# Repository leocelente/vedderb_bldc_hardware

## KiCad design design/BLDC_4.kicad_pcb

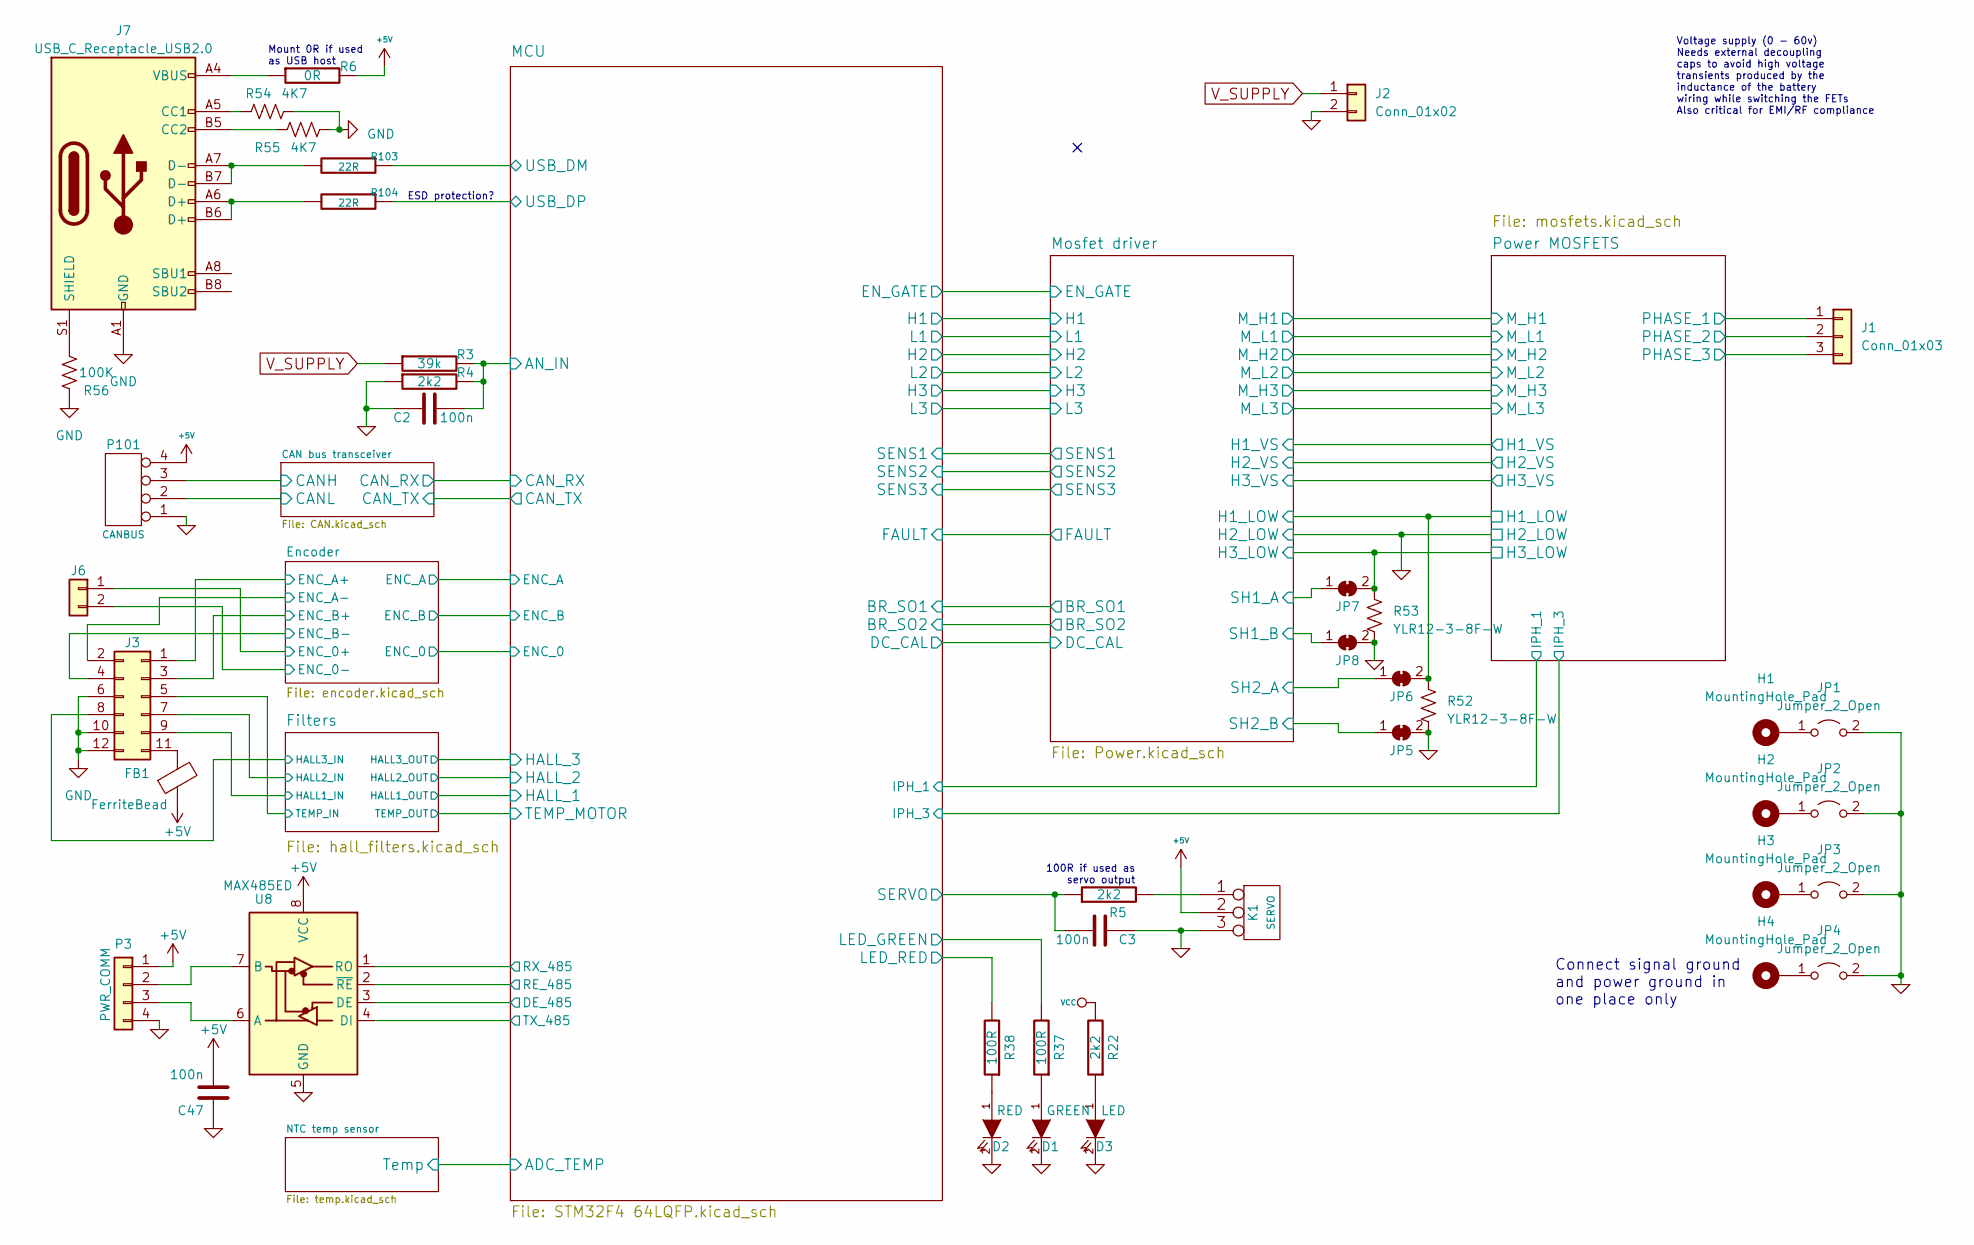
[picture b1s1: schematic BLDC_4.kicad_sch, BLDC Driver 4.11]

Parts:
C2, C3, C47: 100n; SMD-0603_c
D1: GREEN; LED-0603
D2: RED; LED-0603
D3: LED; LED-0603
FB1: FerriteBead; R_0805_2012Metric
H1, H2, H3, H4: MountingHole_Pad; MountingHole_3.2mm_M3_ISO7380_Pad
J1: Conn_01x03; PhoenixContact_MSTBA_2,5_3-G-5,08_1x03_P5.08mm_Horizontal
J2: Conn_01x02; PhoenixContact_MSTBA_2,5_2-G-5,08_1x02_P5.08mm_Horizontal
J3: Conn_02x06_Odd_Even; JST_PHD_S12B-PHDSS_2x06_P2.00mm_Horizontal
J6: Conn_02x06_Odd_Even; JST_PH_S2B-PH-K_1x02_P2.00mm_Horizontal
J7: USB_C_Receptacle_USB2.0; USB_C_Receptacle_G-Switch_GT-USB-7010ASV
JP1, JP2, JP3, JP4: Jumper_2_Open; SolderJumper-2_P1.3mm_Open_Pad1.0x1.5mm
JP5, JP6, JP7, JP8: SolderJumper_2_Bridged; MicroNetSep
K1: SERVO; PinHeader_1x03_P2.54mm_Horizontal
P3: PWR_COMM; JST_PH_S4B-PH-K_1x04_P2.00mm_Horizontal
P101: CANBUS; JST_PH_S4B-PH-K_1x04_P2.00mm_Horizontal
R3: 39k; SMD-0603_r
R4, R5, R22: 2k2; SMD-0603_r
R6: 0R; SMD-0603_r
R37, R38: 100R; SMD-0603_r
R52, R53: YLR12-3-8F-W; YLR2512_G4
R54, R55: 4K7; R_0603_1608Metric_Pad0.98x0.95mm_HandSolder
R56: 100K; R_0603_1608Metric_Pad0.98x0.95mm_HandSolder
R103, R104: 22R; SMD-0603_r
U8: MAX485ED; SOIC-8_3.9x4.9mm_P1.27mm

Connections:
+5V: C47.2, FB1.1, K1.2 (PM), P3.1, P101.4, R6.2, U8.8 (VCC); also elsewhere on the board
/CAN bus transceiver/CANH: P101.3; also elsewhere on the board
/CAN bus transceiver/CANL: P101.2; also elsewhere on the board
/Encoder/ENC_0+: J6.1; also elsewhere on the board
/Encoder/ENC_0-: J6.2; also elsewhere on the board
/Encoder/ENC_A+: J3.1; also elsewhere on the board
/Encoder/ENC_A-: J3.2; also elsewhere on the board
/Encoder/ENC_B+: J3.3; also elsewhere on the board
/Encoder/ENC_B-: J3.4; also elsewhere on the board
/Filters/HALL1_IN: J3.9; also elsewhere on the board
/Filters/HALL2_IN: J3.7; also elsewhere on the board
/Filters/HALL3_IN: J3.8; also elsewhere on the board
/Filters/TEMP_MOTOR: J3.5; also elsewhere on the board
/MCU/AN_IN: C2.2, R3.2, R4.2; also elsewhere on the board
/MCU/DE_485: U8.3 (DE); also elsewhere on the board
/MCU/LED_GREEN: R37.2; also elsewhere on the board
/MCU/LED_RED: R38.2; also elsewhere on the board
/MCU/RE_485: U8.2 (~RE); also elsewhere on the board
/MCU/RX_485: U8.1 (RO); also elsewhere on the board
/MCU/SERVO: C3.2, R5.1; also elsewhere on the board
/MCU/TX_485: U8.4 (DI); also elsewhere on the board
/MCU/USB_DM: R103.1; also elsewhere on the board
/MCU/USB_DP: R104.1; also elsewhere on the board
/Mosfet driver/H1_LOW: JP6.2 (B), R52.1; also elsewhere on the board
/Mosfet driver/H2_VS: J1.2; also elsewhere on the board
/Mosfet driver/SH1_A: JP7.1 (A); also elsewhere on the board
/Mosfet driver/SH2_A: JP6.1 (A); also elsewhere on the board
/Mosfet driver/SH2_B: JP5.1 (A); also elsewhere on the board
/Power MOSFETS/PHASE_1: J1.1; also elsewhere on the board
/Power MOSFETS/PHASE_3: J1.3; also elsewhere on the board
unnamed: D1.1 (A), R37.1
unnamed: D2.1 (A), R38.1
unnamed: D3.1 (A), R22.1
unnamed: FB1.2, J3.11
unnamed: J7.A5 (CC1), R54.1
unnamed: J7.B5 (CC2), R55.1
unnamed: J7.A6 (D+), J7.B6 (D+), R104.2
unnamed: J7.A7 (D-), J7.B7 (D-), R103.2
unnamed: J7.S1 (SHIELD), R56.2
unnamed: J7.A4 (VBUS), J7.A9 (VBUS), J7.B4 (VBUS), J7.B9 (VBUS), R6.1
unnamed: H1.1, JP1.1 (A)
unnamed: H2.1, JP2.1 (A)
unnamed: H3.1, JP3.1 (A)
unnamed: H4.1, JP4.1 (A)
unnamed: K1.1, R5.2
unnamed: P3.2, U8.7 (B)
unnamed: P3.3, U8.6 (A)
VCC: R22.2; also elsewhere on the board
V_SUPPLY: J2.1, R3.1; also elsewhere on the board

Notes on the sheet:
100R if used as servo output
Voltage supply (0 - 60v) Needs external decoupling caps to avoid high voltage transients produced by the inductance of the battery wiring while switching the FETs Also critical for EMI/RF compliance
Connect signal ground and power ground in one place only
Mount 0R if used as USB host
ESD protection?

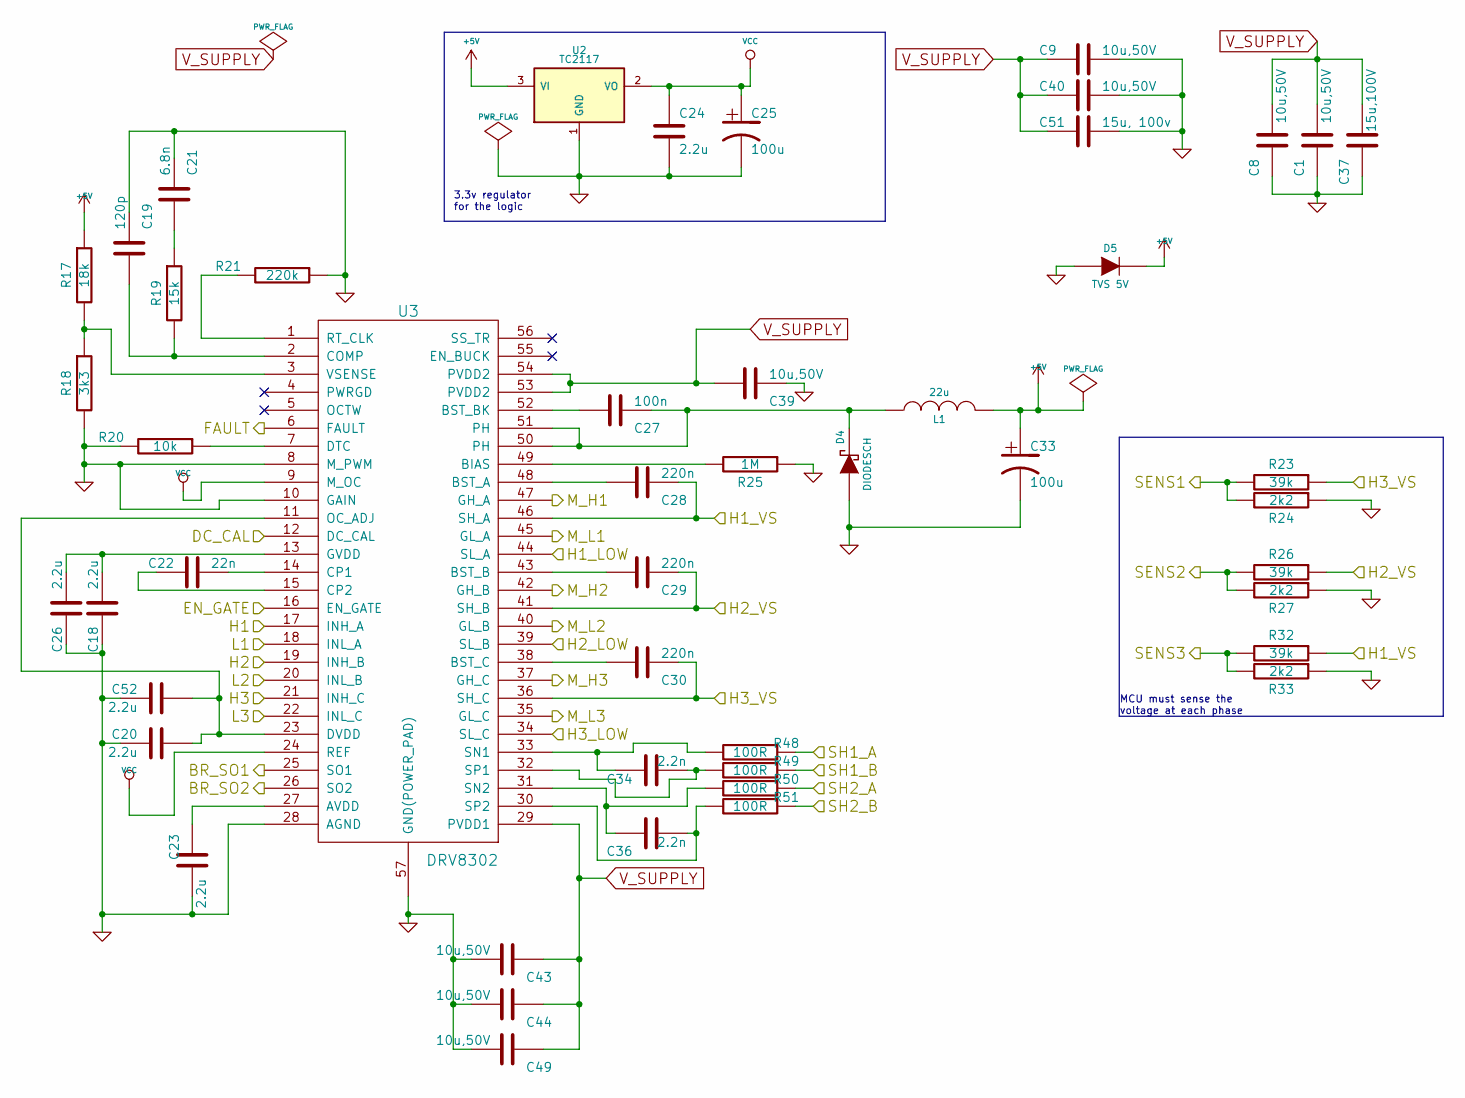
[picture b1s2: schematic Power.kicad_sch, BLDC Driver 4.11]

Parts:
C1, C8, C9, C40, C43, C44, C49: 10u,50V; SMD-1206
C18, C20, C23, C24, C26, C52: 2.2u; SMD-0603_c
C19: 120p; SMD-0603_c
C21: 6.8n; SMD-0603_c
C22: 22n; SMD-0603_c
C25, C33: 100u; c_tant_B
C27: 100n; SMD-0603_c
C28, C29, C30: 220n; SMD-0603_c
C34, C36: 2.2n; SMD-0603_c
C37: 15u,100V; c_2220
C39: 10u,50V; C_1206_3216Metric_Pad1.33x1.80mm_HandSolder
C51: 15u, 100v; c_2220
D4: DIODESCH; SMA_Handsoldering
D5: TVS 5V; do214ac
L1: 22u; inductor_smd_8x5mm
R17: 18k; SMD-0603_r
R18: 3k3; SMD-0603_r
R19: 15k; SMD-0603_r
R20: 10k; SMD-0603_r
R21: 220k; SMD-0603_r
R23, R26, R32: 39k; SMD-0603_r
R24, R27, R33: 2k2; SMD-0603_r
R25: 1M; SMD-0603_r
R48, R49, R50, R51: 100R; SMD-0603_r
U2: TC2117; SOT-223
U3: DRV8302; TSSOP-56-PP

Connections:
+5V: C33.1, D5.2 (K), L1.2, R17.1, U2.3 (VI); also elsewhere on the board
/MCU/BR_SO1: U3.25 (SO1); also elsewhere on the board
/MCU/BR_SO2: U3.26 (SO2); also elsewhere on the board
/MCU/DC_CAL: U3.12 (DC_CAL); also elsewhere on the board
/MCU/EN_GATE: U3.16 (EN_GATE); also elsewhere on the board
/MCU/FAULT: U3.6 (FAULT); also elsewhere on the board
/MCU/H1: U3.17 (INH_A); also elsewhere on the board
/MCU/H2: U3.19 (INH_B); also elsewhere on the board
/MCU/H3: U3.21 (INH_C); also elsewhere on the board
/MCU/L1: U3.18 (INL_A); also elsewhere on the board
/MCU/L2: U3.20 (INL_B); also elsewhere on the board
/MCU/L3: U3.22 (INL_C); also elsewhere on the board
/MCU/SENS1: R23.2, R24.2; also elsewhere on the board
/MCU/SENS2: R26.2, R27.2; also elsewhere on the board
/MCU/SENS3: R32.2, R33.2; also elsewhere on the board
/Mosfet driver/H1_LOW: U3.44 (SL_A); also elsewhere on the board
/Mosfet driver/H2_VS: C29.1, R26.1, U3.41 (SH_B); also elsewhere on the board
/Mosfet driver/M_H1: U3.47 (GH_A); also elsewhere on the board
/Mosfet driver/M_H2: U3.42 (GH_B); also elsewhere on the board
/Mosfet driver/M_H3: U3.37 (GH_C); also elsewhere on the board
/Mosfet driver/M_L1: U3.45 (GL_A); also elsewhere on the board
/Mosfet driver/M_L2: U3.40 (GL_B); also elsewhere on the board
/Mosfet driver/M_L3: U3.35 (GL_C); also elsewhere on the board
/Mosfet driver/SH1_A: R48.1; also elsewhere on the board
/Mosfet driver/SH2_A: R50.1; also elsewhere on the board
/Mosfet driver/SH2_B: R51.1; also elsewhere on the board
unnamed: C21.2, R19.1
unnamed: C27.1, D4.2 (K), L1.1, U3.50 (PH), U3.51 (PH)
unnamed: C23.2, U3.27 (AVDD)
unnamed: R25.2, U3.49 (BIAS)
unnamed: C28.2, U3.48 (BST_A)
unnamed: C29.2, U3.43 (BST_B)
unnamed: C27.2, U3.52 (BST_BK)
unnamed: C30.2, U3.38 (BST_C)
unnamed: C19.2, R19.2, U3.2 (COMP)
unnamed: C22.1, U3.14 (CP1)
unnamed: C22.2, U3.15 (CP2)
unnamed: R20.1, U3.7 (DTC)
unnamed: C20.2, C52.2, U3.11 (OC_ADJ), U3.23 (DVDD)
unnamed: C18.1, C26.1, U3.13 (GVDD)
unnamed: R21.2, U3.1 (RT_CLK)
unnamed: C34.1, R48.2, U3.33 (SN1)
unnamed: C36.1, R50.2, U3.31 (SN2)
unnamed: C34.2, R49.2, U3.32 (SP1)
unnamed: C36.2, R51.2, U3.30 (SP2)
unnamed: R17.2, R18.1, U3.3 (VSENSE)
VCC: C24.1, C25.1, U2.2 (VO), U3.9 (M_OC), U3.24 (REF); also elsewhere on the board
V_SUPPLY: C1.2, C8.2, C9.2, C37.2, C39.2, C40.2, C43.1, C44.1, C49.1, C51.2, U3.29 (PVDD1), U3.53 (PVDD2), U3.54 (PVDD2); also elsewhere on the board

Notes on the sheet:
3.3v regulator for the logic
MCU must sense the voltage at each phase

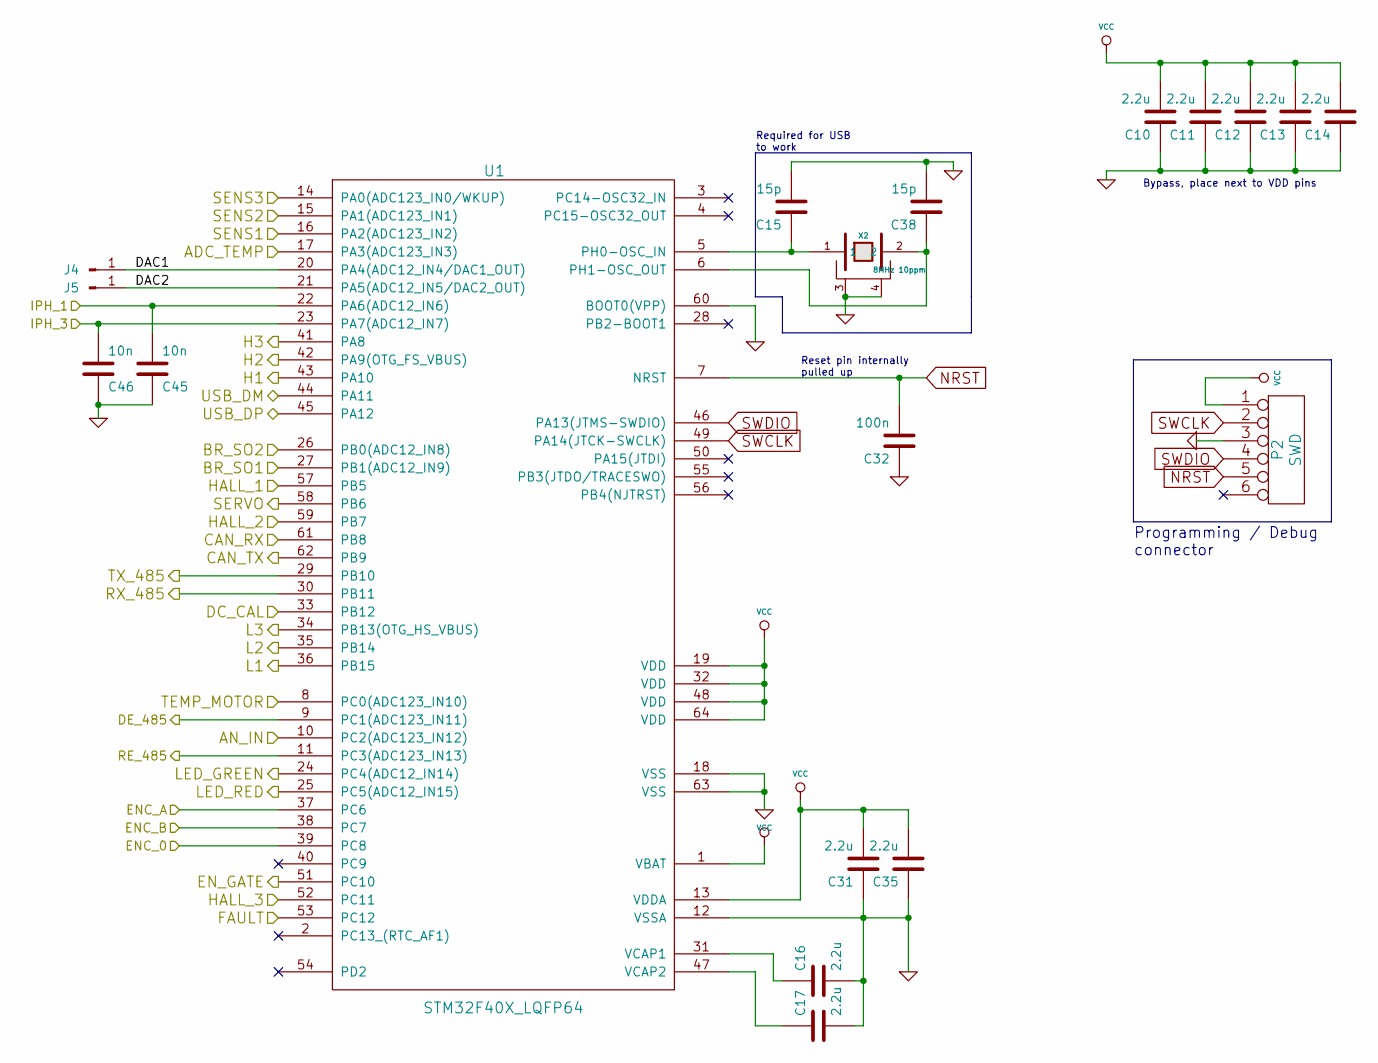
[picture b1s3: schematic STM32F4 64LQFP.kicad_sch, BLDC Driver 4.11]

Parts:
C10, C11, C12, C13, C14, C16, C17, C31, C35: 2.2u; SMD-0603_c
C15, C38: 15p; SMD-0603_c
C32: 100n; SMD-0603_c
C45, C46: 10n; SMD-0603_c
J4, J5: Conn_01x01_Pin; PinHeader_1x01_P1.00mm_Vertical
P2: SWD; JST_PH_B6B-PH-K_1x06_P2.00mm_Vertical
U1: STM32F40X_LQFP64; lqfp64_pad_mod
X2: 8MHz 10ppm; Crystal_5x3mm; mfg# ABM3B-8.0-10-1UT

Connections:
/CAN bus transceiver/CAN_RX: U1.61 (PB8); also elsewhere on the board
/CAN bus transceiver/CAN_TX: U1.62 (PB9); also elsewhere on the board
/Encoder/ENC_0: U1.39 (PC8); also elsewhere on the board
/Encoder/ENC_A: U1.37 (PC6); also elsewhere on the board
/Encoder/ENC_B: U1.38 (PC7); also elsewhere on the board
/Filters/HALL1_OUT: U1.57 (PB5); also elsewhere on the board
/Filters/HALL2_OUT: U1.59 (PB7); also elsewhere on the board
/Filters/HALL3_OUT: U1.52 (PC11); also elsewhere on the board
/Filters/TEMP_MOTOR: U1.8 (PC0(ADC123_IN10)); also elsewhere on the board
/MCU/ADC_TEMP: U1.17 (PA3(ADC123_IN3)); also elsewhere on the board
/MCU/AN_IN: U1.10 (PC2(ADC123_IN12)); also elsewhere on the board
/MCU/BR_SO1: U1.27 (PB1(ADC12_IN9)); also elsewhere on the board
/MCU/BR_SO2: U1.26 (PB0(ADC12_IN8)); also elsewhere on the board
/MCU/DAC1: J4.1, U1.20 (PA4(ADC12_IN4/DAC1_OUT))
/MCU/DAC2: J5.1, U1.21 (PA5(ADC12_IN5/DAC2_OUT))
/MCU/DC_CAL: U1.33 (PB12); also elsewhere on the board
/MCU/DE_485: U1.9 (PC1(ADC123_IN11)); also elsewhere on the board
/MCU/EN_GATE: U1.51 (PC10); also elsewhere on the board
/MCU/FAULT: U1.53 (PC12); also elsewhere on the board
/MCU/H1: U1.43 (PA10); also elsewhere on the board
/MCU/H2: U1.42 (PA9(OTG_FS_VBUS)); also elsewhere on the board
/MCU/H3: U1.41 (PA8); also elsewhere on the board
/MCU/IPH_1: C45.2, U1.22 (PA6(ADC12_IN6)); also elsewhere on the board
/MCU/IPH_3: C46.2, U1.23 (PA7(ADC12_IN7)); also elsewhere on the board
/MCU/L1: U1.36 (PB15); also elsewhere on the board
/MCU/L2: U1.35 (PB14); also elsewhere on the board
/MCU/L3: U1.34 (PB13(OTG_HS_VBUS)); also elsewhere on the board
/MCU/LED_GREEN: U1.24 (PC4(ADC12_IN14)); also elsewhere on the board
/MCU/LED_RED: U1.25 (PC5(ADC12_IN15)); also elsewhere on the board
/MCU/RE_485: U1.11 (PC3(ADC123_IN13)); also elsewhere on the board
/MCU/RX_485: U1.30 (PB11); also elsewhere on the board
/MCU/SENS1: U1.16 (PA2(ADC123_IN2)); also elsewhere on the board
/MCU/SENS2: U1.15 (PA1(ADC123_IN1)); also elsewhere on the board
/MCU/SENS3: U1.14 (PA0(ADC123_IN0/WKUP)); also elsewhere on the board
/MCU/SERVO: U1.58 (PB6); also elsewhere on the board
/MCU/TX_485: U1.29 (PB10); also elsewhere on the board
/MCU/USB_DM: U1.44 (PA11); also elsewhere on the board
/MCU/USB_DP: U1.45 (PA12); also elsewhere on the board
NRST: C32.2, P2.5, U1.7 (NRST)
unnamed: C15.1, U1.5 (PH0-OSC_IN), X2.1
unnamed: C38.1, U1.6 (PH1-OSC_OUT), X2.2
unnamed: C16.1, U1.31 (VCAP1)
unnamed: C17.1, U1.47 (VCAP2)
SWCLK: P2.2, U1.49 (PA14(JTCK-SWCLK))
SWDIO: P2.4, U1.46 (PA13(JTMS-SWDIO))
VCC: C10.2, C11.2, C12.2, C13.2, C14.2, C31.2, C35.2, P2.1, U1.1 (VBAT), U1.13 (VDDA), U1.19 (VDD), U1.32 (VDD), U1.48 (VDD), U1.64 (VDD); also elsewhere on the board

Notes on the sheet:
Bypass, place next to VDD pins
Required for USB to work
Programming / Debug connector
Reset pin internally pulled up

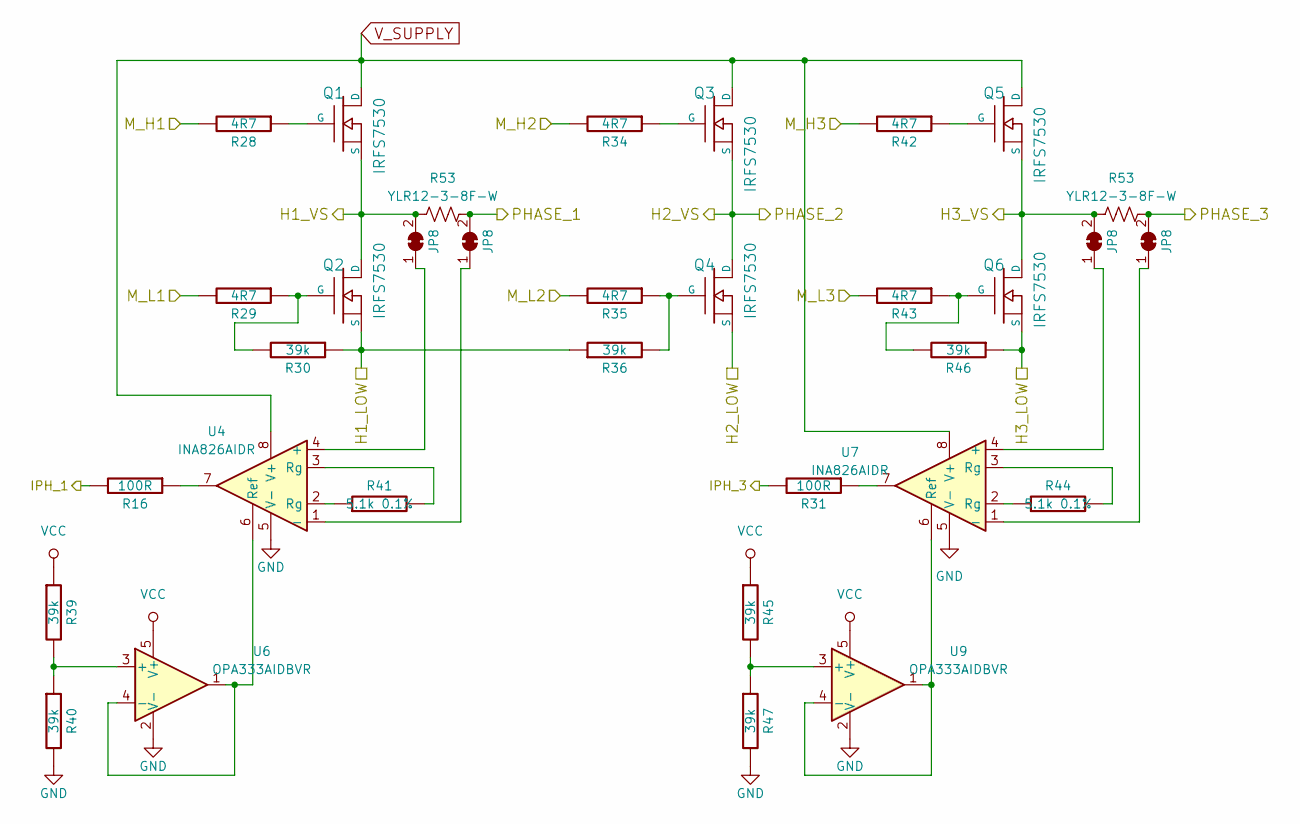
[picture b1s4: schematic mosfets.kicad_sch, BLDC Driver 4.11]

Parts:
JP8: SolderJumper_2_Bridged; MicroNetSep
Q1, Q2, Q3, Q4, Q5, Q6: IRFS7530; D2PAK-7-GDS
R16, R31: 100R; SMD-0603_r
R28, R29, R34, R35, R42, R43: 4R7; SMD-0603_r
R30, R36, R39, R40, R45, R46, R47: 39k; SMD-0603_r
R41, R44: 5.1k 0.1%; SMD-0603_r
R53: YLR12-3-8F-W; YLR2512_G4
U4, U7: INA826AIDR; SOIC-8_3.9x4.9mm_P1.27mm
U6, U9: OPA333AIDBVR; SOT-23-5

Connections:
/MCU/IPH_1: R16.2; also elsewhere on the board
/MCU/IPH_3: R31.2; also elsewhere on the board
/Mosfet driver/H1_LOW: Q2.S, R30.1, R36.1; also elsewhere on the board
/Mosfet driver/H2_VS: Q3.S, Q4.D; also elsewhere on the board
/Mosfet driver/M_H1: R28.2; also elsewhere on the board
/Mosfet driver/M_H2: R34.2; also elsewhere on the board
/Mosfet driver/M_H3: R42.2; also elsewhere on the board
/Mosfet driver/M_L1: R29.2; also elsewhere on the board
/Mosfet driver/M_L2: R35.2; also elsewhere on the board
/Mosfet driver/M_L3: R43.2; also elsewhere on the board
unnamed: Q1.G, R28.1
unnamed: Q2.G, R29.1, R30.2
unnamed: Q3.G, R34.1
unnamed: Q4.G, R35.1, R36.2
unnamed: Q5.G, R42.1
unnamed: Q6.G, R43.1, R46.2
unnamed: R16.1, U4.7
unnamed: R31.1, U7.7
unnamed: R41.1, U4.2 (Rg)
unnamed: R41.2, U4.3 (Rg)
unnamed: R44.1, U7.2 (Rg)
unnamed: R44.2, U7.3 (Rg)
unnamed: U4.6 (Ref), U6.1, U6.4 (-)
unnamed: R39.2, R40.1, U6.3 (+)
unnamed: U7.6 (Ref), U9.1, U9.4 (-)
unnamed: R45.2, R47.1, U9.3 (+)
VCC: R39.1, R45.1, U6.5 (V+), U9.5 (V+); also elsewhere on the board
V_SUPPLY: Q1.D, Q3.D, Q5.D, U4.8 (V+), U7.8 (V+); also elsewhere on the board

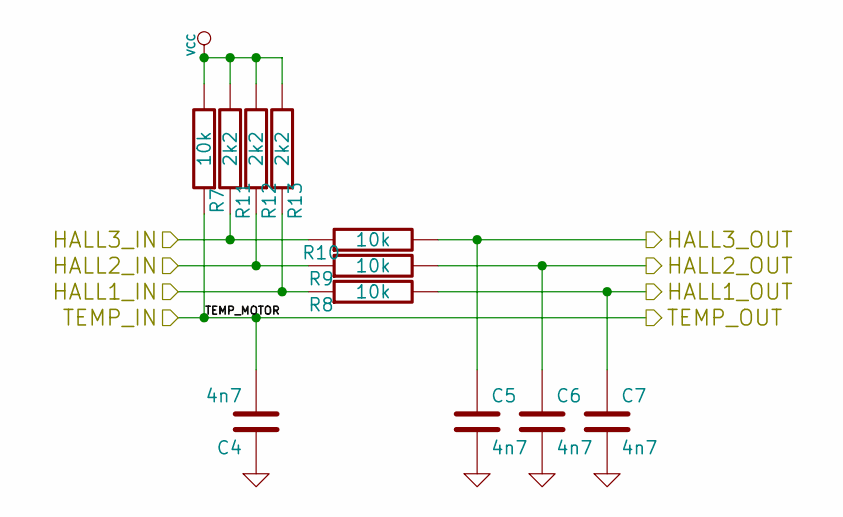
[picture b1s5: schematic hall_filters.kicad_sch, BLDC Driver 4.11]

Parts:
C4, C5, C6, C7: 4n7; SMD-0603_c
R7, R8, R9, R10: 10k; SMD-0603_r
R11, R12, R13: 2k2; SMD-0603_r

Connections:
/Filters/HALL1_IN: R8.1, R13.1; also elsewhere on the board
/Filters/HALL1_OUT: C7.1, R8.2; also elsewhere on the board
/Filters/HALL2_IN: R9.1, R12.1; also elsewhere on the board
/Filters/HALL2_OUT: C6.1, R9.2; also elsewhere on the board
/Filters/HALL3_IN: R10.1, R11.1; also elsewhere on the board
/Filters/HALL3_OUT: C5.1, R10.2; also elsewhere on the board
/Filters/TEMP_MOTOR: C4.2, R7.1; also elsewhere on the board
VCC: R7.2, R11.2, R12.2, R13.2; also elsewhere on the board

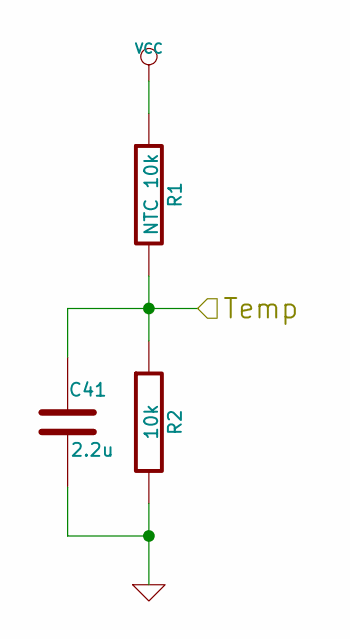
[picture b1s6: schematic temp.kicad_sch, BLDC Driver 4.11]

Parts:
C41: 2.2u; SMD-0603_c
R1: NTC 10k; SMD-0603_r
R2: 10k; SMD-0603_r

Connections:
/MCU/ADC_TEMP: C41.1, R1.2, R2.1; also elsewhere on the board
VCC: R1.1; also elsewhere on the board

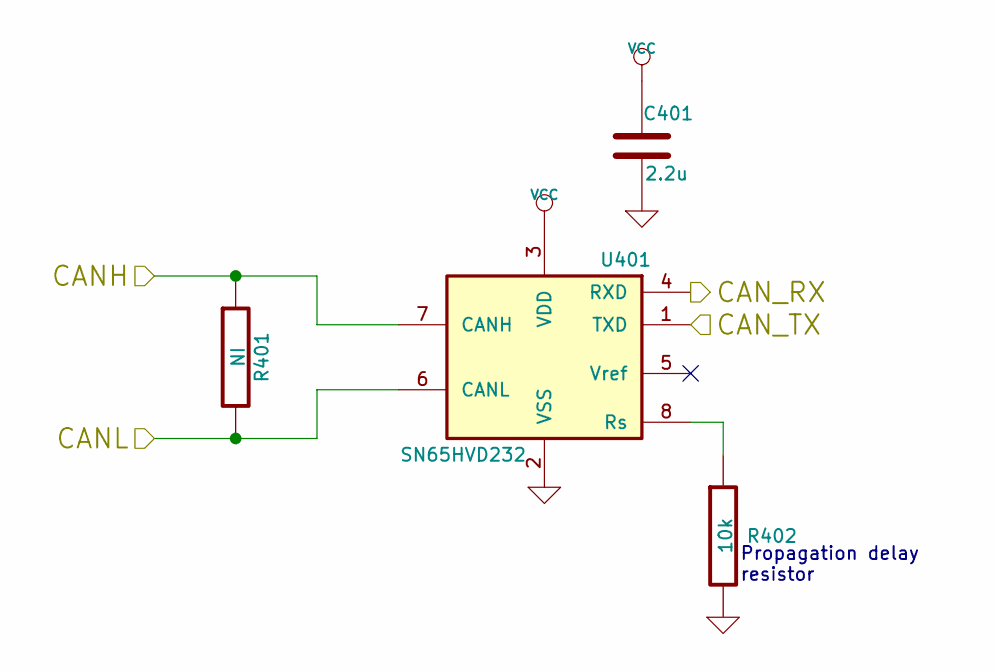
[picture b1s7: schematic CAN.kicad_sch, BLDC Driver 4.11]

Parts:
C401: 2.2u; SMD-0603_c
R401: NI; SMD-0603_r
R402: 10k; SMD-0603_r
U401: SN65HVD232; SOIC-8-W

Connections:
/CAN bus transceiver/CANH: R401.1, U401.7 (CANH); also elsewhere on the board
/CAN bus transceiver/CANL: R401.2, U401.6 (CANL); also elsewhere on the board
/CAN bus transceiver/CAN_RX: U401.4 (RXD); also elsewhere on the board
/CAN bus transceiver/CAN_TX: U401.1 (TXD); also elsewhere on the board
unnamed: R402.1, U401.8 (Rs)
VCC: C401.1, U401.3 (VDD); also elsewhere on the board

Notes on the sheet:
Propagation delay resistor

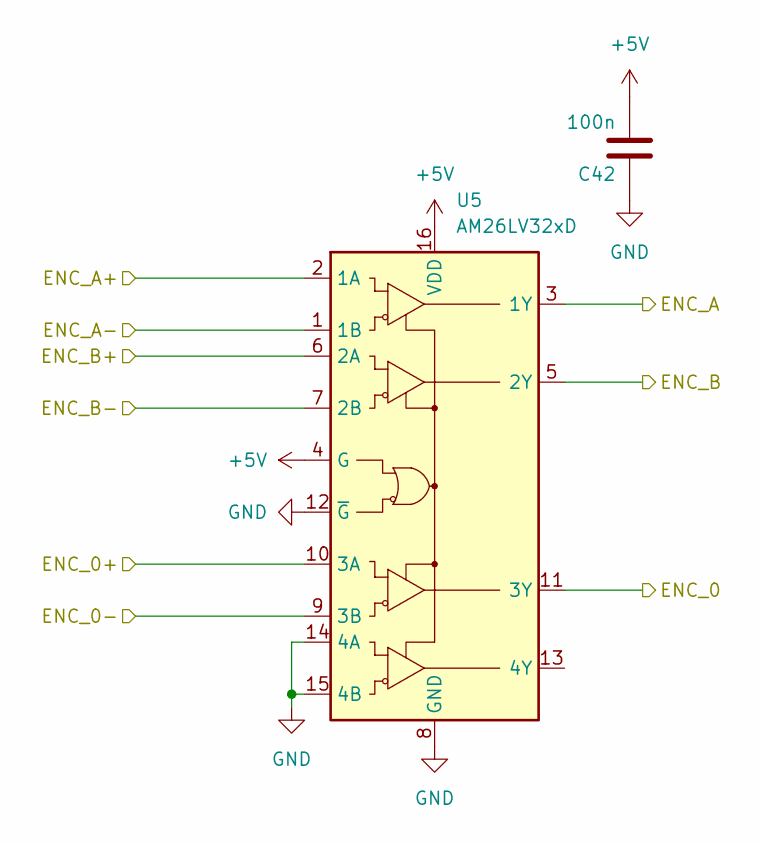
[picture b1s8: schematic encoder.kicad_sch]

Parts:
C42: 100n; SMD-0603_c
U5: AM26LV32xD; SOIC-16_3.9x9.9mm_P1.27mm

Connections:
+5V: C42.2, U5.4 (G), U5.16 (VDD); also elsewhere on the board
/Encoder/ENC_0: U5.11 (3Y); also elsewhere on the board
/Encoder/ENC_0+: U5.10 (3A); also elsewhere on the board
/Encoder/ENC_0-: U5.9 (3B); also elsewhere on the board
/Encoder/ENC_A: U5.3 (1Y); also elsewhere on the board
/Encoder/ENC_A+: U5.2 (1A); also elsewhere on the board
/Encoder/ENC_A-: U5.1 (1B); also elsewhere on the board
/Encoder/ENC_B: U5.5 (2Y); also elsewhere on the board
/Encoder/ENC_B+: U5.6 (2A); also elsewhere on the board
/Encoder/ENC_B-: U5.7 (2B); also elsewhere on the board

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
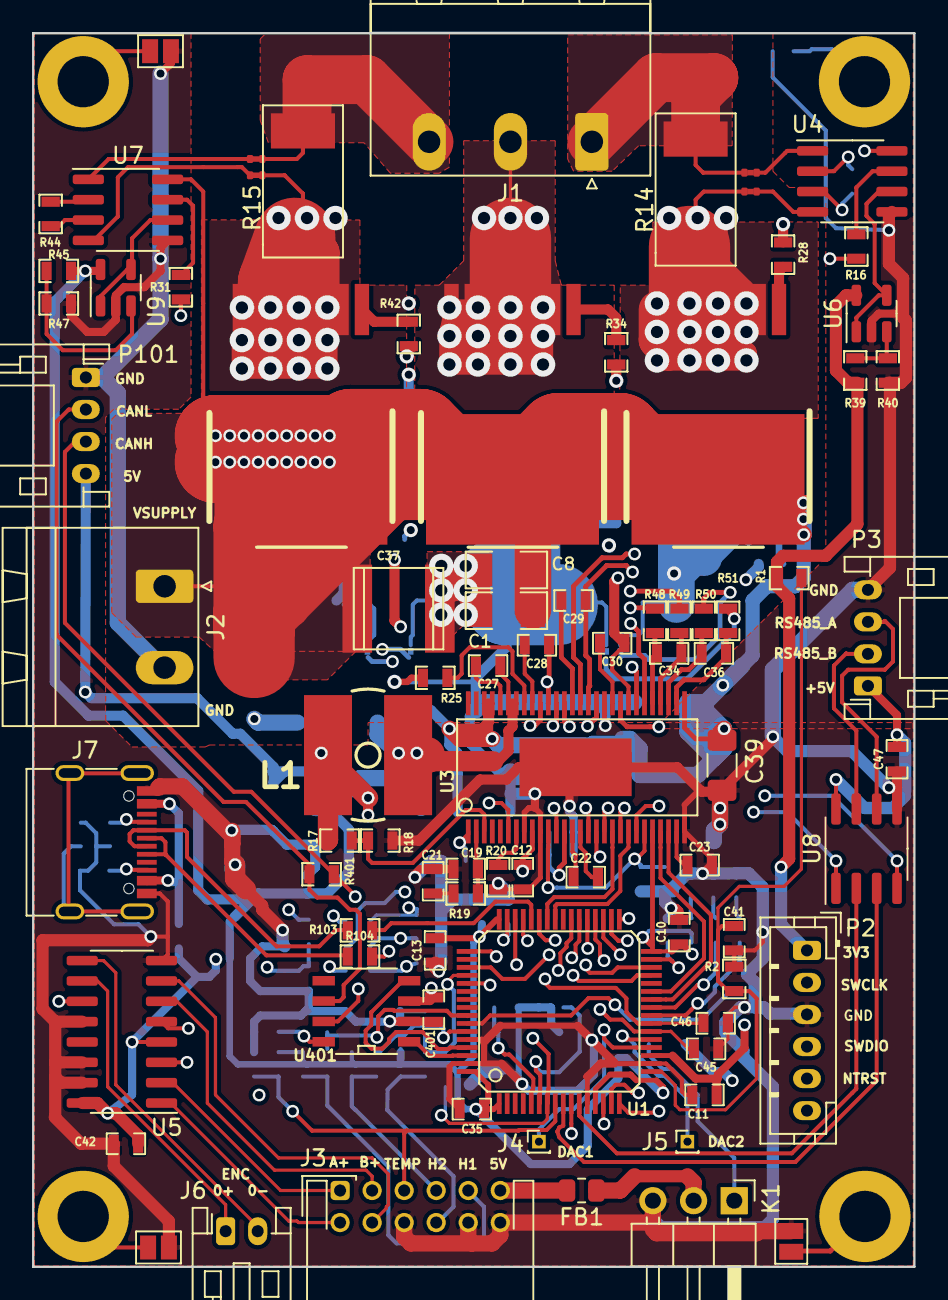
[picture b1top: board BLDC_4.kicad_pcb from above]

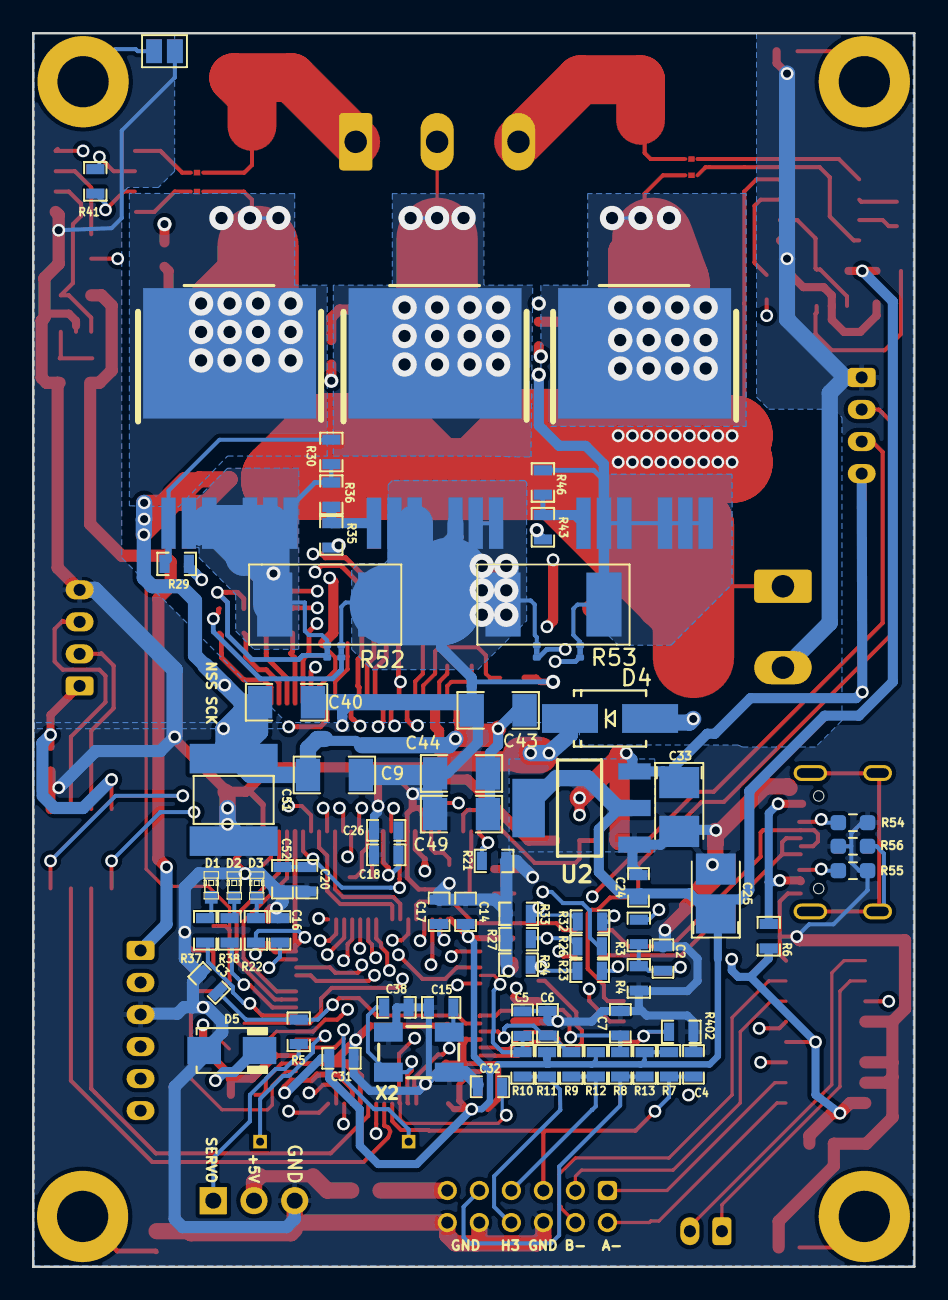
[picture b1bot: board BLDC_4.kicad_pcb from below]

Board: 4 copper layers, 55.0 x 77.0 mm, 162 parts (75 on the bottom side), 135 nets.

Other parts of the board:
JP9, JP10, JP11, JP12: SolderJumper_2_Bridged; MicroNetSep
R14, R15: YLR12-3-8F-W; YLR2512_G4

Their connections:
/Power MOSFETS/PHASE_1: JP11.2 (B), R14.2; also elsewhere on the board
/Power MOSFETS/PHASE_3: JP10.2 (B), R15.2; also elsewhere on the board

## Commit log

2023-01-20 Going to KiCAD 6
2023-02-25 Adding more 3D models
2023-02-25 Moving to KICAD 6
2023-02-26 STM pins connected
2023-02-27 Última versão de hoje
2023-02-28 Corrigindo Footprints com silk nos pads
2023-02-28 Limpando warnings e DRC errors
2023-02-28 Don't need to track gerbers!
2023-02-28 Bill of materials
2023-02-28 Final 20230228
2023-03-01 Fixing voltage supply of INA826 to read phase current value
2023-03-06 Fixing mini-USB connector pinout
2023-03-07 Changing to USB-C connector
2023-03-11 Swapped SERVO and SENS1 pins
